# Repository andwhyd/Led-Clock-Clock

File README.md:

# LED Clock Clock
Ongoing project to create a less mechanical [Clock Clock](https://clockclock.com/collections/clockclock-24) clone.

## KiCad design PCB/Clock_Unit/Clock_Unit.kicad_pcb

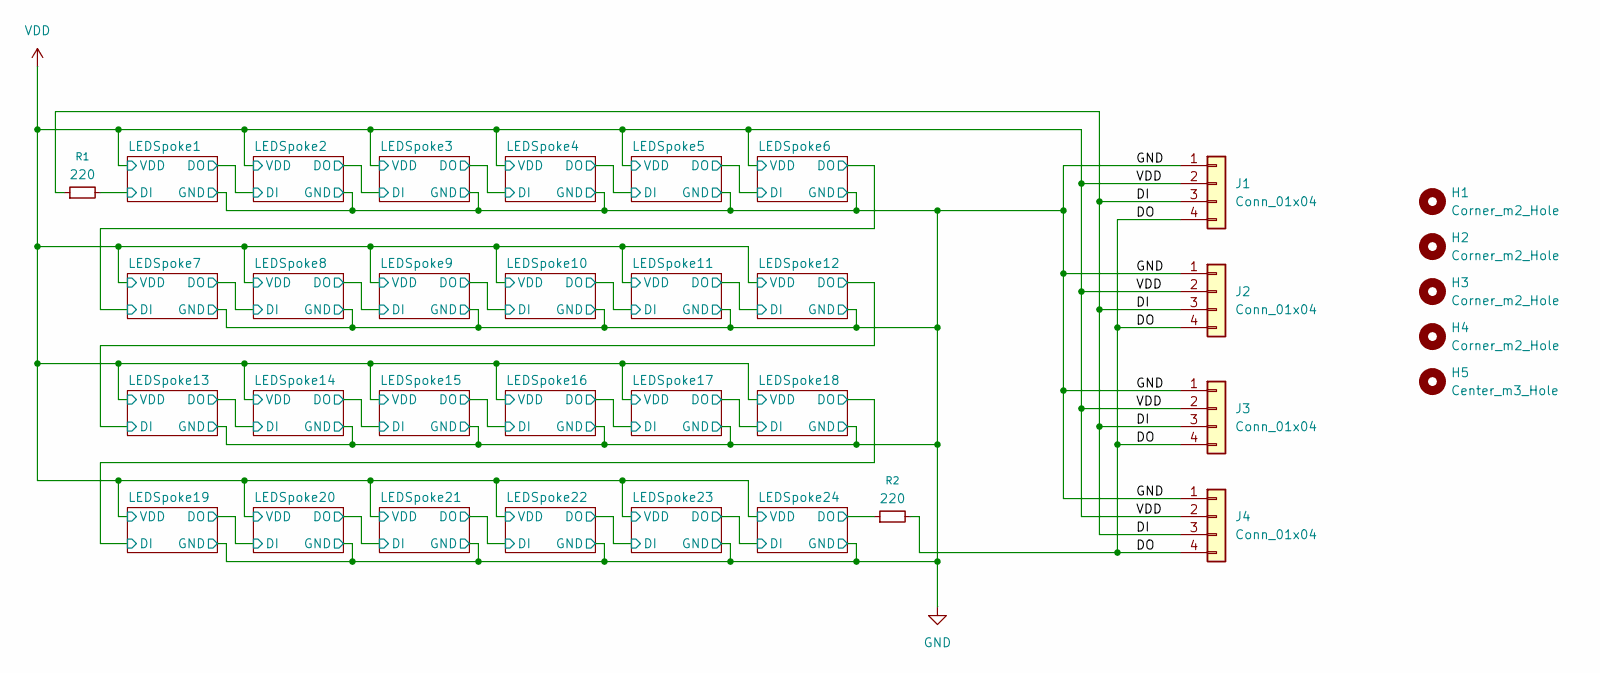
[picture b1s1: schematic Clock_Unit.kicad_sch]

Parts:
H1, H2, H3, H4: Corner_m2_Hole; MountingHole_2.2mm_M2
H5: Center_m3_Hole; MountingHole_3.2mm_M3
J1, J2, J3, J4: Conn_01x04; PinHeader_1x04_P2.54mm_Vertical
R1, R2: 220; R_0402_1005Metric_Pad0.72x0.64mm_HandSolder

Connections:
/DI: J1.3, J2.3, J3.3, J4.3, R1.1
/DO: J1.4, J2.4, J3.4, J4.4, R2.2
/LEDSpoke1/DI: R1.2; also elsewhere on the board
/LEDSpoke24/DO: R2.1; also elsewhere on the board
GND: J1.1, J2.1, J3.1, J4.1; also elsewhere on the board
VDD: J1.2, J2.2, J3.2, J4.2; also elsewhere on the board

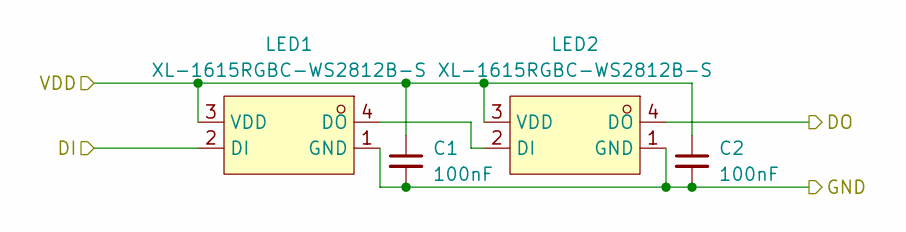
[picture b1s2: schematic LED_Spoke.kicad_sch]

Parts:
C1, C2: 100nF; C_0402_1005Metric_Pad0.74x0.62mm_HandSolder
LED1, LED2: XL-1615RGBC-WS2812B-S; LED-SMD_4P-L1.6-W1.5_XL-1615RGBC-WS2812B-S; LCSC Part C41413180

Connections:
/LEDSpoke1/DI: LED1.2 (DI); also elsewhere on the board
/LEDSpoke1/DO: LED2.4 (DO); also elsewhere on the board
GND: C1.2, C2.2, LED1.1 (GND), LED2.1 (GND); also elsewhere on the board
unnamed: LED1.4 (DO), LED2.2 (DI)
VDD: C1.1, C2.1, LED1.3 (VDD), LED2.3 (VDD); also elsewhere on the board

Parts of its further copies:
C3, C4, C5, C6, C7, C8, C9, C10, C11, C12, C13, C14, C15, C16, C17, C18, C19, C20, C21, C22, C23, C24, C25, C26, C27, C28, C29, C30, C31, C32, C33, C34, C35, C36, C37, C38, C39, C40, C41, C42, C43, C44, C45, C46, C47, C48: 100nF; C_0402_1005Metric_Pad0.74x0.62mm_HandSolder
LED3, LED4, LED5, LED6, LED7, LED8, LED9, LED10, LED11, LED12, LED13, LED14, LED15, LED16, LED17, LED18, LED19, LED20, LED21, LED22, LED23, LED24, LED25, LED26, LED27, LED28, LED29, LED30, LED31, LED32, LED33, LED34, LED35, LED36, LED37, LED38, LED39, LED40, LED41, LED42, LED43, LED44, LED45, LED46, LED47, LED48: XL-1615RGBC-WS2812B-S; LED-SMD_4P-L1.6-W1.5_XL-1615RGBC-WS2812B-S; LCSC Part C41413180

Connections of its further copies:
/LEDSpoke1/DO: LED3.2 (DI); also elsewhere on the board
/LEDSpoke2/DO: LED4.4 (DO), LED5.2 (DI)
/LEDSpoke3/DO: LED6.4 (DO), LED7.2 (DI)
/LEDSpoke4/DO: LED8.4 (DO), LED9.2 (DI)
/LEDSpoke5/DO: LED10.4 (DO), LED11.2 (DI)
/LEDSpoke6/DO: LED12.4 (DO), LED13.2 (DI)
/LEDSpoke7/DO: LED14.4 (DO), LED15.2 (DI)
/LEDSpoke8/DO: LED16.4 (DO), LED17.2 (DI)
/LEDSpoke10/DI: LED18.4 (DO), LED19.2 (DI)
/LEDSpoke10/DO: LED20.4 (DO), LED21.2 (DI)
/LEDSpoke11/DO: LED22.4 (DO), LED23.2 (DI)
/LEDSpoke12/DO: LED24.4 (DO), LED25.2 (DI)
/LEDSpoke13/DO: LED26.4 (DO), LED27.2 (DI)
/LEDSpoke14/DO: LED28.4 (DO), LED29.2 (DI)
/LEDSpoke15/DO: LED30.4 (DO), LED31.2 (DI)
/LEDSpoke16/DO: LED32.4 (DO), LED33.2 (DI)
/LEDSpoke17/DO: LED34.4 (DO), LED35.2 (DI)
/LEDSpoke18/DO: LED36.4 (DO), LED37.2 (DI)
/LEDSpoke19/DO: LED38.4 (DO), LED39.2 (DI)
/LEDSpoke20/DO: LED40.4 (DO), LED41.2 (DI)
/LEDSpoke21/DO: LED42.4 (DO), LED43.2 (DI)
/LEDSpoke22/DO: LED44.4 (DO), LED45.2 (DI)
/LEDSpoke23/DO: LED46.4 (DO), LED47.2 (DI)
/LEDSpoke24/DO: LED48.4 (DO); also elsewhere on the board
GND: C3.2, C4.2, C5.2, C6.2, C7.2, C8.2, C9.2, C10.2, C11.2, C12.2, C13.2, C14.2, C15.2, C16.2, C17.2, C18.2, C19.2, C20.2, C21.2, C22.2, C23.2, C24.2, C25.2, C26.2, C27.2, C28.2, C29.2, C30.2, C31.2, C32.2, C33.2, C34.2, C35.2, C36.2, C37.2, C38.2, C39.2, C40.2, C41.2, C42.2, C43.2, C44.2, C45.2, C46.2, C47.2, C48.2, LED3.1 (GND), LED4.1 (GND), LED5.1 (GND), LED6.1 (GND), LED7.1 (GND), LED8.1 (GND), LED9.1 (GND), LED10.1 (GND), LED11.1 (GND), LED12.1 (GND), LED13.1 (GND), LED14.1 (GND), LED15.1 (GND), LED16.1 (GND), LED17.1 (GND), LED18.1 (GND), LED19.1 (GND), LED20.1 (GND), LED21.1 (GND), LED22.1 (GND), LED23.1 (GND), LED24.1 (GND), LED25.1 (GND), LED26.1 (GND), LED27.1 (GND), LED28.1 (GND), LED29.1 (GND), LED30.1 (GND), LED31.1 (GND), LED32.1 (GND), LED33.1 (GND), LED34.1 (GND), LED35.1 (GND), LED36.1 (GND), LED37.1 (GND), LED38.1 (GND), LED39.1 (GND), LED40.1 (GND), LED41.1 (GND), LED42.1 (GND), LED43.1 (GND), LED44.1 (GND), LED45.1 (GND), LED46.1 (GND), LED47.1 (GND), LED48.1 (GND); also elsewhere on the board
unnamed: LED3.4 (DO), LED4.2 (DI)
unnamed: LED5.4 (DO), LED6.2 (DI)
unnamed: LED7.4 (DO), LED8.2 (DI)
unnamed: LED9.4 (DO), LED10.2 (DI)
unnamed: LED11.4 (DO), LED12.2 (DI)
unnamed: LED13.4 (DO), LED14.2 (DI)
unnamed: LED15.4 (DO), LED16.2 (DI)
unnamed: LED17.4 (DO), LED18.2 (DI)
unnamed: LED19.4 (DO), LED20.2 (DI)
unnamed: LED21.4 (DO), LED22.2 (DI)
unnamed: LED23.4 (DO), LED24.2 (DI)
unnamed: LED25.4 (DO), LED26.2 (DI)
unnamed: LED27.4 (DO), LED28.2 (DI)
unnamed: LED29.4 (DO), LED30.2 (DI)
unnamed: LED31.4 (DO), LED32.2 (DI)
unnamed: LED33.4 (DO), LED34.2 (DI)
unnamed: LED35.4 (DO), LED36.2 (DI)
unnamed: LED37.4 (DO), LED38.2 (DI)
unnamed: LED39.4 (DO), LED40.2 (DI)
unnamed: LED41.4 (DO), LED42.2 (DI)
unnamed: LED43.4 (DO), LED44.2 (DI)
unnamed: LED45.4 (DO), LED46.2 (DI)
unnamed: LED47.4 (DO), LED48.2 (DI)
VDD: C3.1, C4.1, C5.1, C6.1, C7.1, C8.1, C9.1, C10.1, C11.1, C12.1, C13.1, C14.1, C15.1, C16.1, C17.1, C18.1, C19.1, C20.1, C21.1, C22.1, C23.1, C24.1, C25.1, C26.1, C27.1, C28.1, C29.1, C30.1, C31.1, C32.1, C33.1, C34.1, C35.1, C36.1, C37.1, C38.1, C39.1, C40.1, C41.1, C42.1, C43.1, C44.1, C45.1, C46.1, C47.1, C48.1, LED3.3 (VDD), LED4.3 (VDD), LED5.3 (VDD), LED6.3 (VDD), LED7.3 (VDD), LED8.3 (VDD), LED9.3 (VDD), LED10.3 (VDD), LED11.3 (VDD), LED12.3 (VDD), LED13.3 (VDD), LED14.3 (VDD), LED15.3 (VDD), LED16.3 (VDD), LED17.3 (VDD), LED18.3 (VDD), LED19.3 (VDD), LED20.3 (VDD), LED21.3 (VDD), LED22.3 (VDD), LED23.3 (VDD), LED24.3 (VDD), LED25.3 (VDD), LED26.3 (VDD), LED27.3 (VDD), LED28.3 (VDD), LED29.3 (VDD), LED30.3 (VDD), LED31.3 (VDD), LED32.3 (VDD), LED33.3 (VDD), LED34.3 (VDD), LED35.3 (VDD), LED36.3 (VDD), LED37.3 (VDD), LED38.3 (VDD), LED39.3 (VDD), LED40.3 (VDD), LED41.3 (VDD), LED42.3 (VDD), LED43.3 (VDD), LED44.3 (VDD), LED45.3 (VDD), LED46.3 (VDD), LED47.3 (VDD), LED48.3 (VDD); also elsewhere on the board

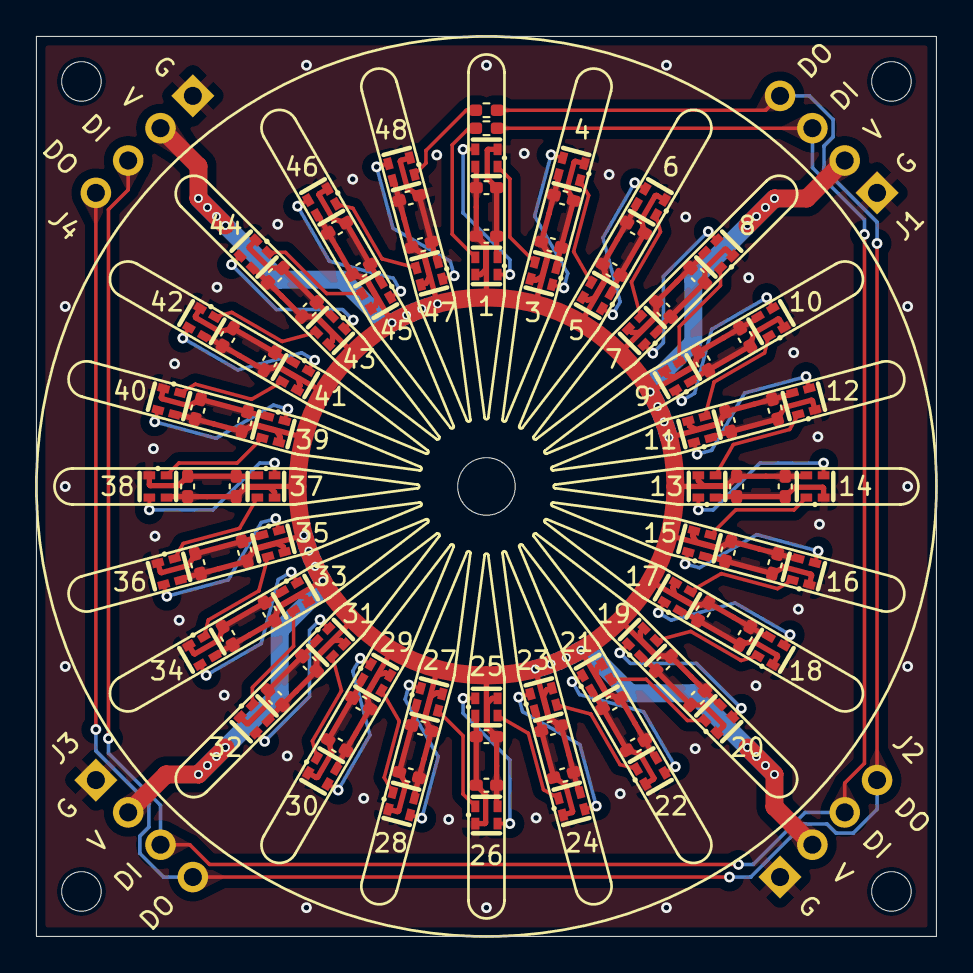
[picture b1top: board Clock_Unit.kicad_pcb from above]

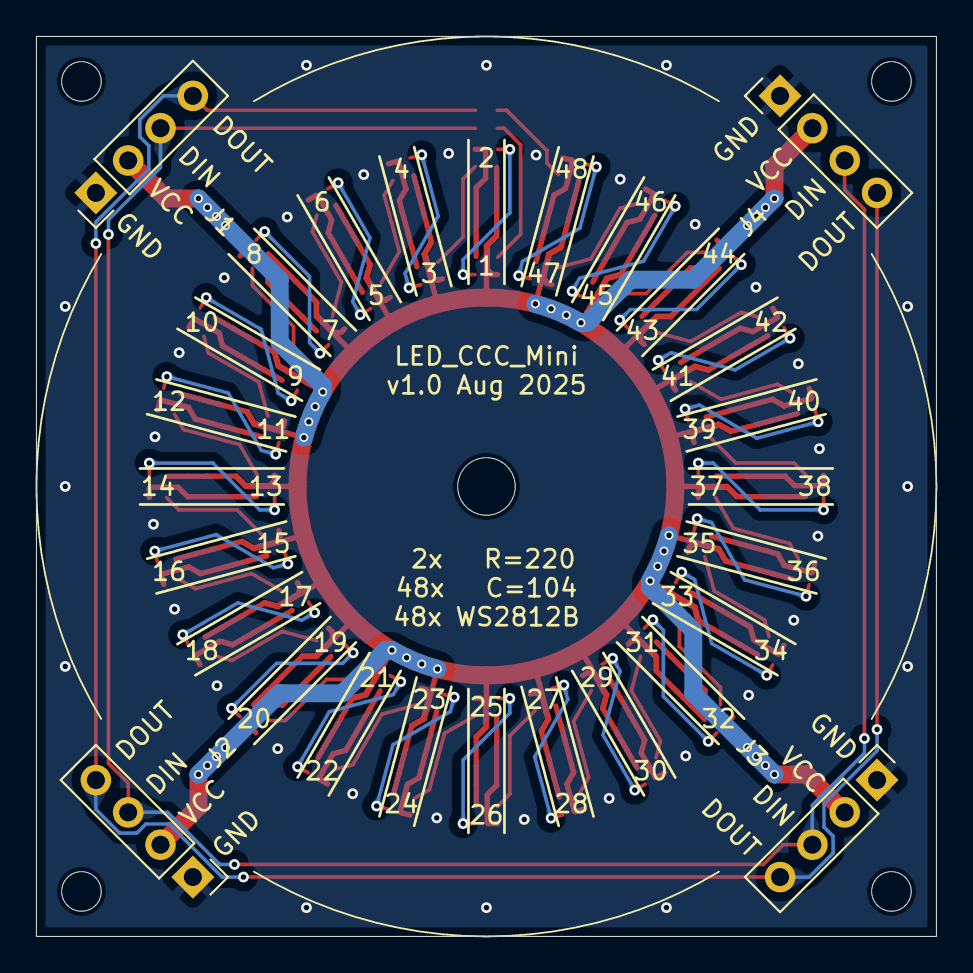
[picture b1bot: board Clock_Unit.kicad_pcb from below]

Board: 2 copper layers, 50.0 x 50.0 mm, 107 parts (4 on the bottom side), 53 nets.

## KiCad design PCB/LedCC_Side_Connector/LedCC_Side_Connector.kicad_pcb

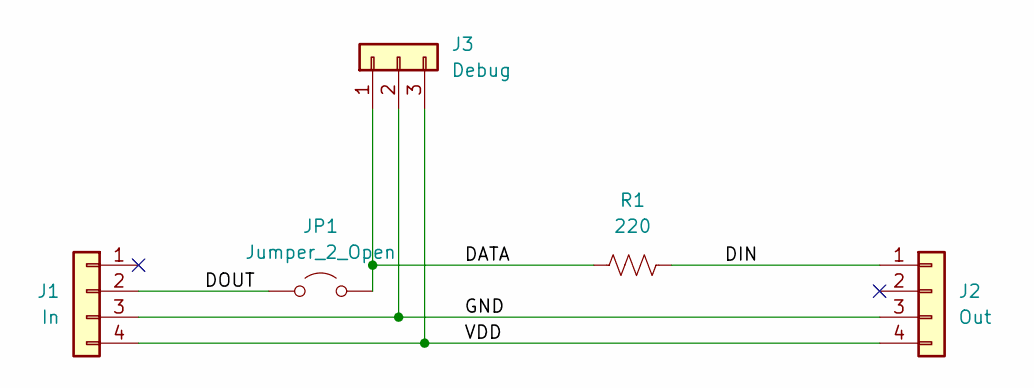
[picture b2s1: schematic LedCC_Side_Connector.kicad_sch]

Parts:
J1: In; HDR-TH_4P-P1.27-V-F-R2-C2-S1.27
J2: Out; HDR-TH_4P-P1.27-V-F-R2-C2-S1.27
J3: Debug; PinSocket_1x03_P2.54mm_Vertical
JP1: Jumper_2_Open; SolderJumper-2_P1.3mm_Open_RoundedPad1.0x1.5mm
R1: 220; R_0603_1608Metric

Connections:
/DATA: J3.1, JP1.2 (B), R1.1
/DIN: J2.1, R1.2
/DOUT: J1.2, JP1.1 (A)
/GND: J1.3, J2.3, J3.2
/VDD: J1.4, J2.4, J3.3

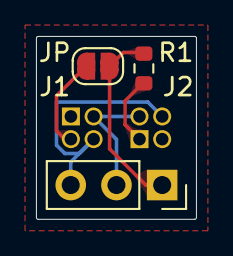
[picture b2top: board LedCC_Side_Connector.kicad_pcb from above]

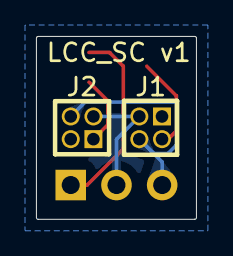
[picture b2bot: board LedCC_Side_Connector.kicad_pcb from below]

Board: 2 copper layers, 8.9 x 10.2 mm, 5 parts (2 on the bottom side), 5 nets.

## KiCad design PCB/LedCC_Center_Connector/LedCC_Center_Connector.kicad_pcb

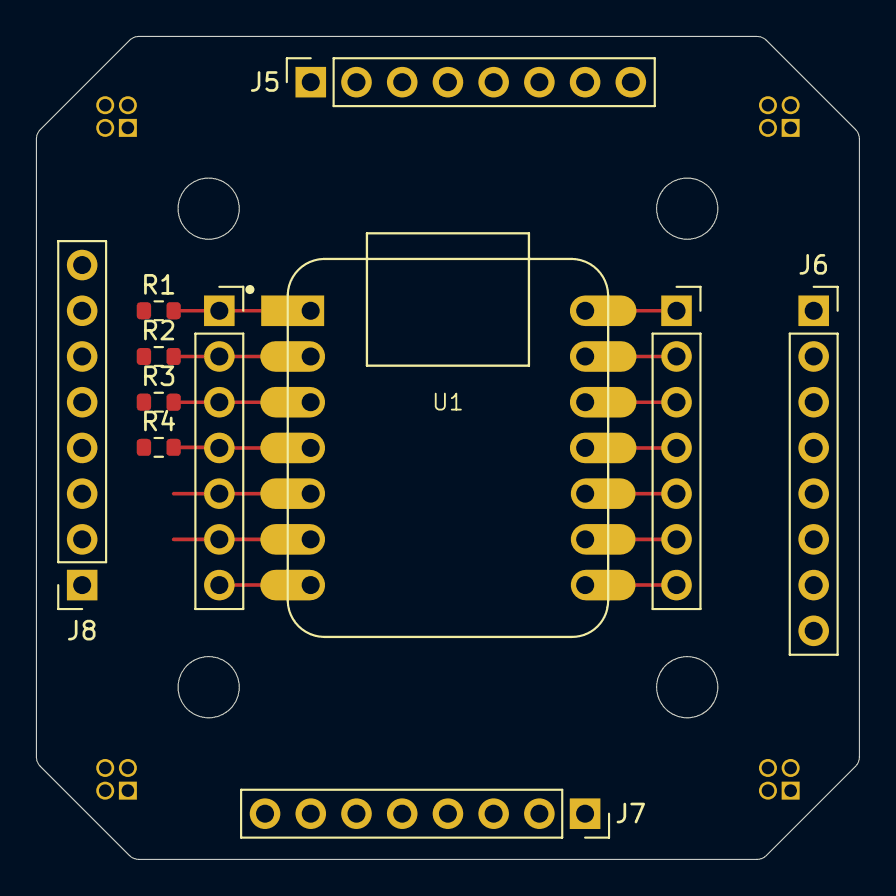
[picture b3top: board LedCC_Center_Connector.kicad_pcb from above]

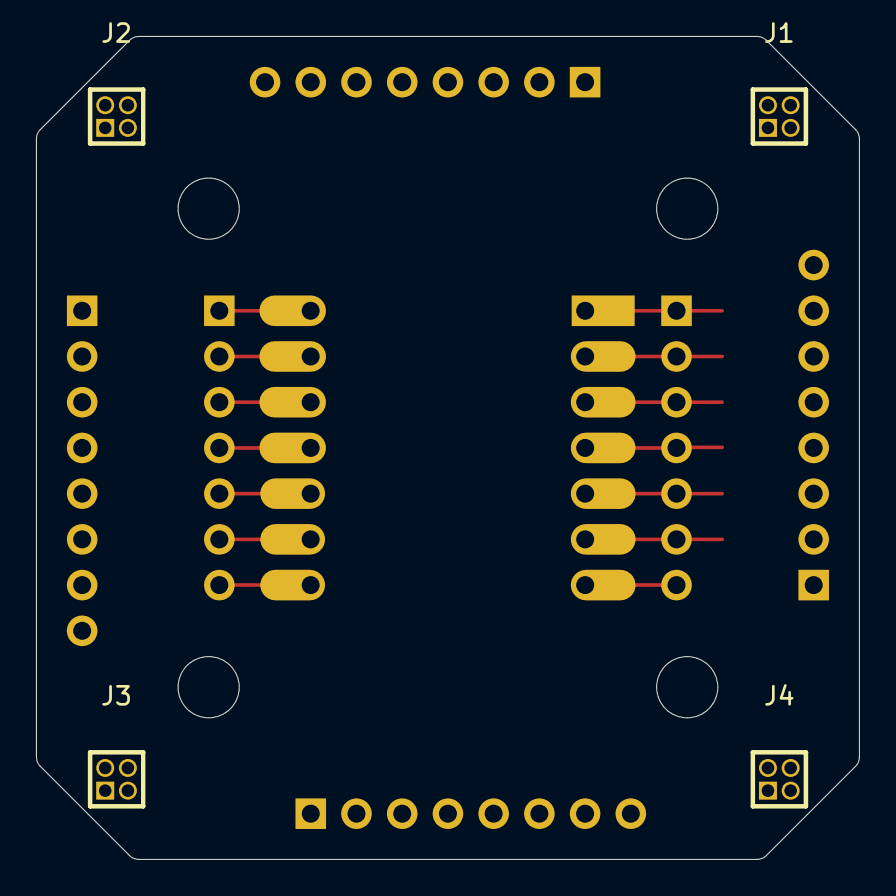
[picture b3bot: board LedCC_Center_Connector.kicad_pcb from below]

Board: 2 copper layers, 45.7 x 45.7 mm, 15 parts (4 on the bottom side), 18 nets.

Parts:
J1: LED1; HDR-TH_4P-P1.27-V-F-R2-C2-S1.27
J2: LED2; HDR-TH_4P-P1.27-V-F-R2-C2-S1.27
J3: LED3; HDR-TH_4P-P1.27-V-F-R2-C2-S1.27
J4: LED4; HDR-TH_4P-P1.27-V-F-R2-C2-S1.27
J5, J6, J7, J8: Conn_01x06; PinSocket_1x08_P2.54mm_Vertical
J9, J10: Conn_01x07; PinSocket_1x07_P2.54mm_Vertical
R1, R2, R3, R4: 220; R_0603_1608Metric
U1: Seeed Studio XIAO SAMD21; XIAO-Generic-Hybrid-14P-2.54-21X17.8MM

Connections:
/DIN1: J1.1, R1.1
/DIN2: J2.1, R2.1
/DIN3: J3.1, R3.1
/DIN4: J4.1, R4.1
/GND: J1.4, J2.4, J3.4, J4.4, J5.2, J6.2, J7.2, J8.2, J10.1, U1.14 (5V)
/VDD: J1.3, J2.3, J3.3, J4.3, J5.1, J6.1, J7.1, J8.1, J10.2, U1.13 (GND)
unnamed: J5.3, J6.3, J7.3, J8.3, J9.1, U1.1 (PA02_A0_D0)
unnamed: J5.4, J6.4, J7.4, J8.4, J9.2, U1.2 (PA4_A1_D1)
unnamed: J5.5, J6.5, J7.5, J8.5, J9.3, U1.3 (PA10_A2_D2)
unnamed: J5.6, J6.6, J7.6, J8.6, J9.4, U1.4 (PA11_A3_D3)
unnamed: J5.7, J6.7, J7.7, J8.7, J9.5, U1.5 (PA8_A4_D4_SDA)
unnamed: J5.8, J6.8, J7.8, J8.8, J9.6, U1.6 (PA9_A5_D5_SCL)
unnamed: J9.7, U1.7 (PB08_A6_D6_TX)
unnamed: J10.3, U1.12 (3V3)
unnamed: J10.4, U1.11 (PA6_A10_D10_MOSI)
unnamed: J10.5, U1.10 (PA5_A9_D9_MISO)
unnamed: J10.6, U1.9 (PA7_A8_D8_SCK)
unnamed: J10.7, U1.8 (PB09_A7_D7_RX)

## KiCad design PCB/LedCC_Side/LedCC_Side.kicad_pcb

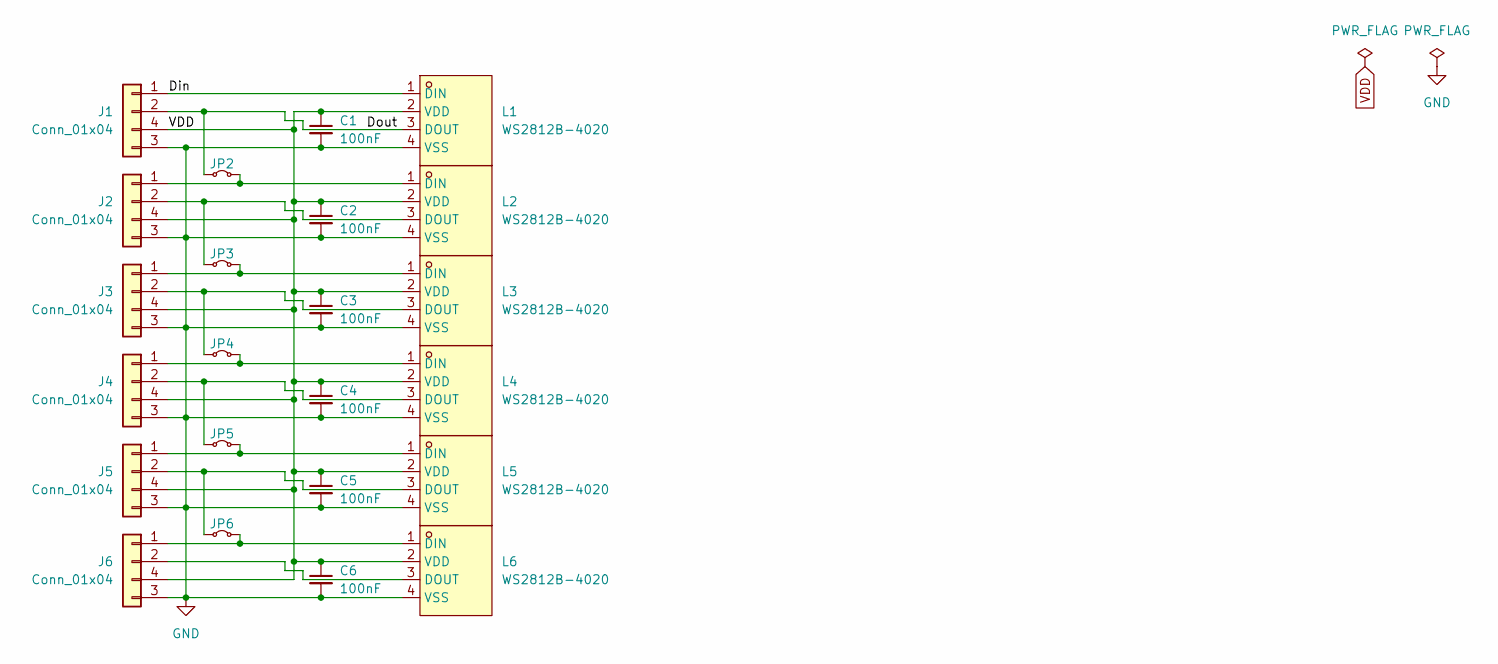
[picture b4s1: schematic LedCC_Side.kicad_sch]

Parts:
C1, C2, C3, C4, C5, C6: 100nF; C_0603_1608Metric
J1, J2, J3, J4, J5, J6: Conn_01x04; HDR-SMD_4P-P1.27-V-M-R2-C2-S1.27-LS5.5
JP2, JP3, JP4, JP5, JP6: Jumper_2_Small_Bridged; SolderJumper-2_P1.3mm_Bridged_RoundedPad1.0x1.5mm
L1, L2, L3, L4, L5, L6: WS2812B-4020; LED-SMD_WS2812B-4020; LCSC Part C965557

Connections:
/Din: J1.1, L1.1 (DIN)
/Dout: J1.2, JP2.1 (A), L1.3 (DOUT)
GND: C1.2, C2.2, C3.2, C4.2, C5.2, C6.2, J1.3, J2.3, J3.3, J4.3, J5.3, J6.3, L1.4 (VSS), L2.4 (VSS), L3.4 (VSS), L4.4 (VSS), L5.4 (VSS), L6.4 (VSS)
unnamed: J2.1, JP2.2 (B), L2.1 (DIN)
unnamed: J2.2, JP3.1 (A), L2.3 (DOUT)
unnamed: J3.1, JP3.2 (B), L3.1 (DIN)
unnamed: J3.2, JP4.1 (A), L3.3 (DOUT)
unnamed: J4.1, JP4.2 (B), L4.1 (DIN)
unnamed: J4.2, JP5.1 (A), L4.3 (DOUT)
unnamed: J5.1, JP5.2 (B), L5.1 (DIN)
unnamed: J5.2, JP6.1 (A), L5.3 (DOUT)
unnamed: J6.1, JP6.2 (B), L6.1 (DIN)
unnamed: J6.2, L6.3 (DOUT)
VDD: C1.1, C2.1, C3.1, C4.1, C5.1, C6.1, J1.4, J2.4, J3.4, J4.4, J5.4, J6.4, L1.2 (VDD), L2.2 (VDD), L3.2 (VDD), L4.2 (VDD), L5.2 (VDD), L6.2 (VDD)

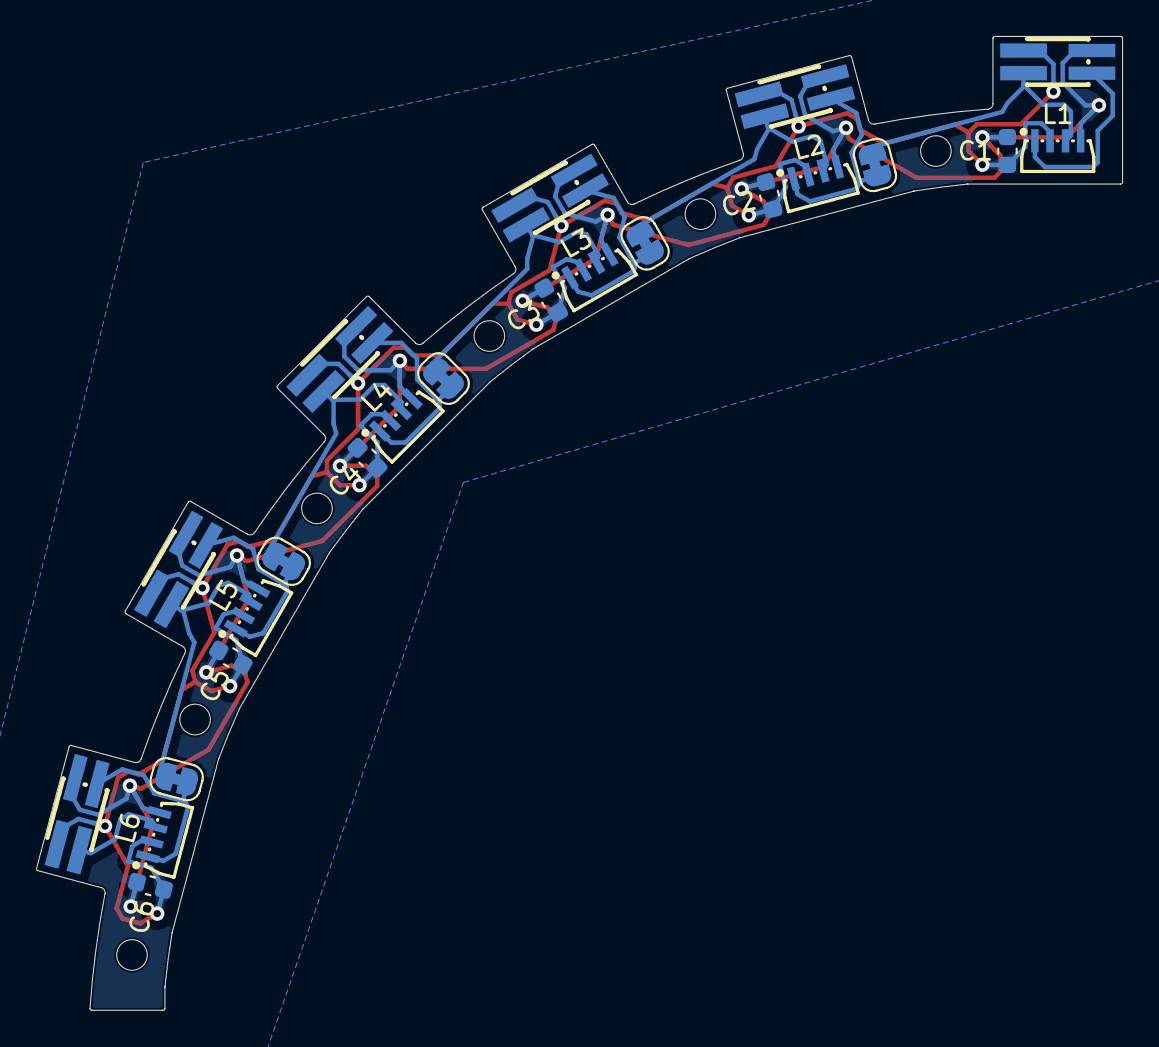
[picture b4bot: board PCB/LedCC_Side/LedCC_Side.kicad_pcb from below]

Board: 2 copper layers, 60.3 x 54.1 mm, 23 parts (23 on the bottom side), 14 nets.

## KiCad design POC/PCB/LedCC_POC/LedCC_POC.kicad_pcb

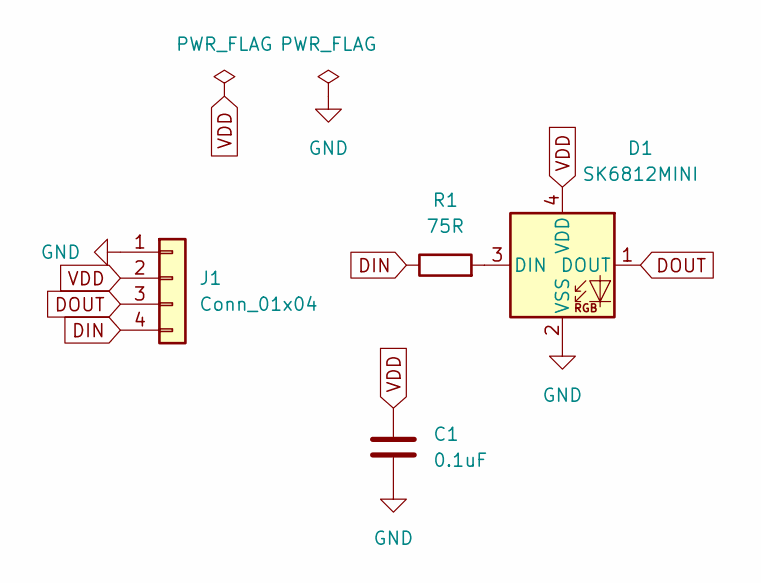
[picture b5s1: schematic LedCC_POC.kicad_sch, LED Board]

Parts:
C1: 0.1uF; C_0805_2012Metric_Pad1.18x1.45mm_HandSolder
D1: SK6812MINI; SK6812-MINI-E
J1: Conn_01x04; SolderWirePad_1x04_SMD_1x2mm
R1: 75R; R_0805_2012Metric_Pad1.20x1.40mm_HandSolder

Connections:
DIN: J1.4, R1.1
DOUT: D1.1 (DOUT), J1.3
GND: C1.1, D1.2 (VSS), J1.1
unnamed: D1.3 (DIN), R1.2
VDD: C1.2, D1.4 (VDD), J1.2

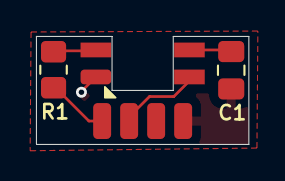
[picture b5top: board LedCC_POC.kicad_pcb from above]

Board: 2 copper layers, 11.8 x 6.0 mm, 4 parts (0 on the bottom side), 5 nets.

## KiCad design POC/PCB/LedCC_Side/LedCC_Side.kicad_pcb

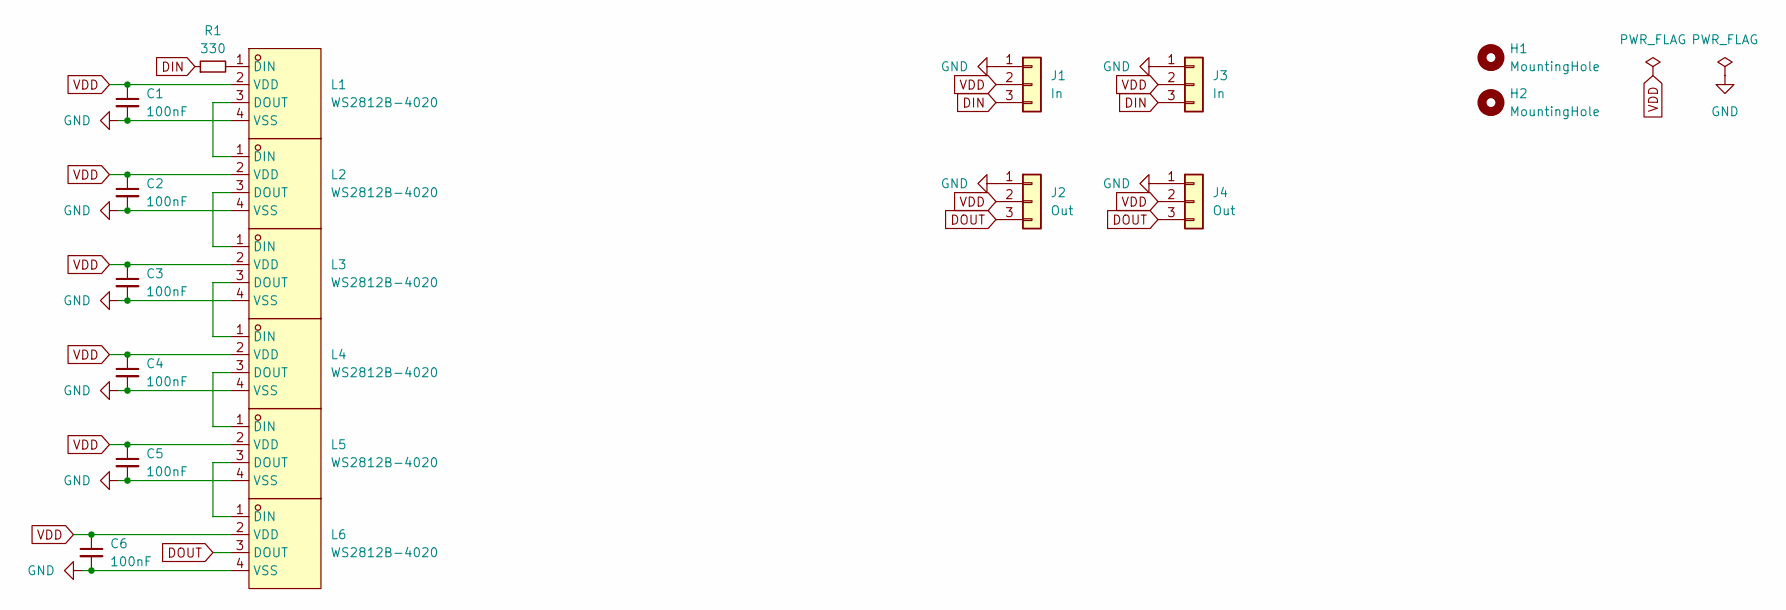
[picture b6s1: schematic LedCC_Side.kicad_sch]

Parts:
C1, C2, C3, C4, C5, C6: 100nF; C_0603_1608Metric
H1, H2: MountingHole; MountingHole_2.2mm_M2
J1, J3: In; Led-Jumper
J2, J4: Out; Led-Jumper
L1, L2, L3, L4, L5, L6: WS2812B-4020; LED-SMD_WS2812B-4020; LCSC Part C965557
R1: 330; R_0603_1608Metric

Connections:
DIN: J1.3, J3.3, R1.1
DOUT: J2.3, J4.3, L6.3 (DOUT)
GND: C1.2, C2.2, C3.2, C4.2, C5.2, C6.2, J1.1, J2.1, J3.1, J4.1, L1.4 (VSS), L2.4 (VSS), L3.4 (VSS), L4.4 (VSS), L5.4 (VSS), L6.4 (VSS)
unnamed: L1.1 (DIN), R1.2
unnamed: L1.3 (DOUT), L2.1 (DIN)
unnamed: L2.3 (DOUT), L3.1 (DIN)
unnamed: L3.3 (DOUT), L4.1 (DIN)
unnamed: L4.3 (DOUT), L5.1 (DIN)
unnamed: L5.3 (DOUT), L6.1 (DIN)
VDD: C1.1, C2.1, C3.1, C4.1, C5.1, C6.1, J1.2, J2.2, J3.2, J4.2, L1.2 (VDD), L2.2 (VDD), L3.2 (VDD), L4.2 (VDD), L5.2 (VDD), L6.2 (VDD)

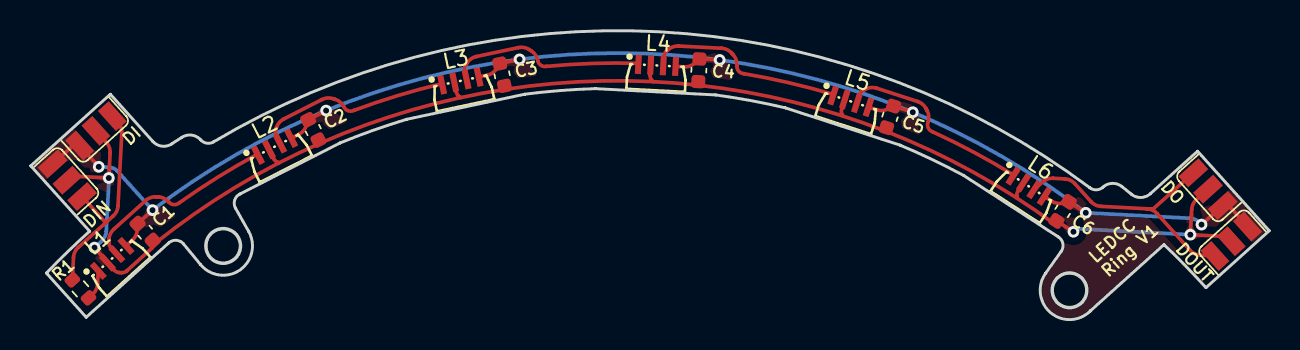
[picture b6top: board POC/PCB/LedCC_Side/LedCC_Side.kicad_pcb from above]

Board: 2 copper layers, 84.5 x 19.7 mm, 19 parts (0 on the bottom side), 10 nets.

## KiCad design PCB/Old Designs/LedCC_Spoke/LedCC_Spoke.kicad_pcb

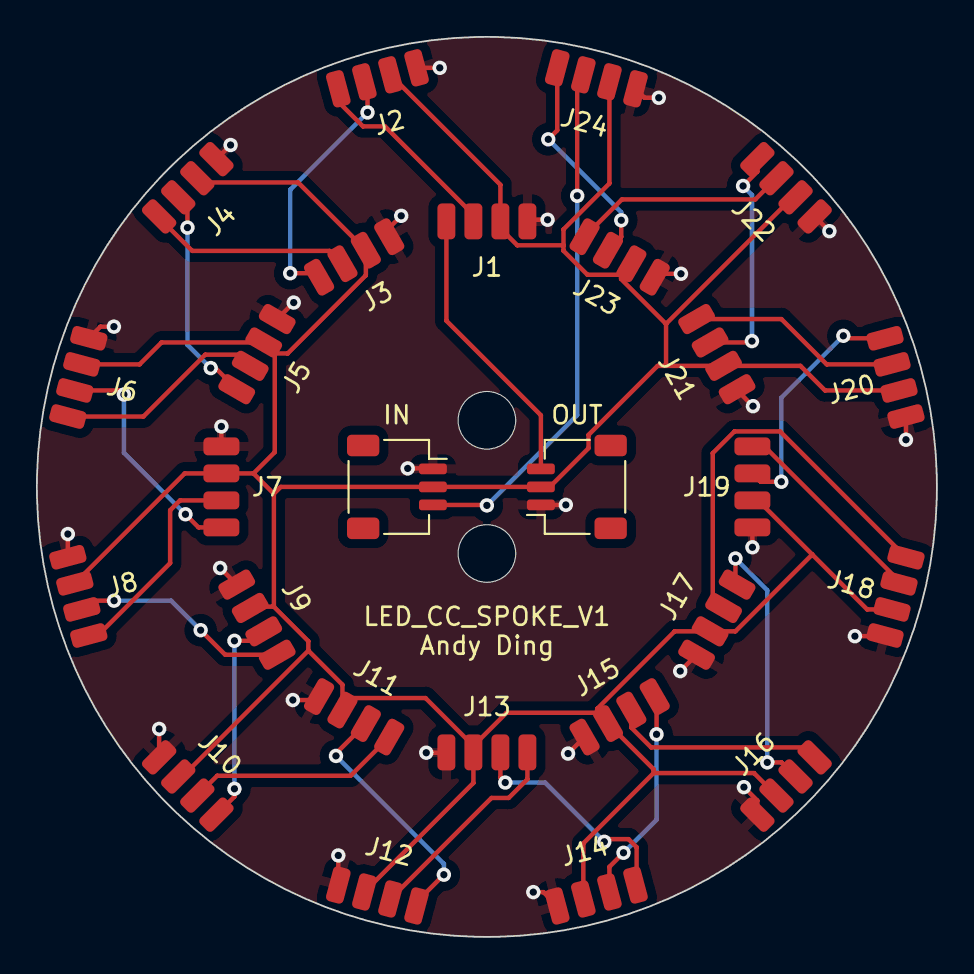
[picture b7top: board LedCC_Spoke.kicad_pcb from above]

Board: 2 copper layers, 50.0 x 50.0 mm, 26 parts (0 on the bottom side), 27 nets.

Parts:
IN: In; JST_SH_SM03B-SRSS-TB_1x03-1MP_P1.00mm_Horizontal
J1, J2, J3, J4, J5, J6, J7, J8, J9, J10, J11, J12, J13, J14, J15, J16, J17, J18, J19, J20, J21, J22, J23, J24: Conn_01x04; SolderWirePad_1x04_SMD_1x2mm
OUT: Out; JST_SH_SM03B-SRSS-TB_1x03-1MP_P1.00mm_Horizontal

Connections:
DIN: IN.3, J24.3
DOUT: J1.4, OUT.3
GND: IN.1, J1.1, J2.1, J3.1, J4.1, J5.1, J6.1, J7.1, J8.1, J9.1, J10.1, J11.1, J12.1, J13.1, J14.1, J15.1, J16.1, J17.1, J18.1, J19.1, J20.1, J21.1, J22.1, J23.1, J24.1, OUT.1
unnamed: J1.3, J2.4
unnamed: J2.3, J3.4
unnamed: J3.3, J4.4
unnamed: J4.3, J5.4
unnamed: J5.3, J6.4
unnamed: J6.3, J7.4
unnamed: J7.3, J8.4
unnamed: J8.3, J9.4
unnamed: J10.3, J11.4
unnamed: J9.3, J10.4
unnamed: J11.3, J12.4
unnamed: J12.3, J13.4
unnamed: J13.3, J14.4
unnamed: J14.3, J15.4
unnamed: J15.3, J16.4
unnamed: J16.3, J17.4
unnamed: J17.3, J18.4
unnamed: J18.3, J19.4
unnamed: J19.3, J20.4
unnamed: J20.3, J21.4
unnamed: J21.3, J22.4
unnamed: J22.3, J23.4
unnamed: J23.3, J24.4
VDD: IN.2, J1.2, J2.2, J3.2, J4.2, J5.2, J6.2, J7.2, J8.2, J9.2, J10.2, J11.2, J12.2, J13.2, J14.2, J15.2, J16.2, J17.2, J18.2, J19.2, J20.2, J21.2, J22.2, J23.2, J24.2, OUT.2

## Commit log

2024-01-01 Update '5' digit
2024-05-20 Add PCB
2024-06-10 Testing code updates
2024-06-10 Reorganize files
2024-06-21 Reorganize
2024-06-21 Prototype digit testing
2024-07-14 PCB Updates
2025-08-18 Pivot to smaller design with simpler PCB
    Change from side lit LEDs and 4 piece circles to 50mm smaller flat PCBs and diffused 1.5mm LEDs
2025-08-18 Increase VDD trace width
    Chanced from 0.3mm to 1mm to support max power draw of all LEDs
2025-08-18 Add center hole
    m3 opening added
2025-08-19 Schematic + PCB Updates
    Corrected LED symbol and improved silkscreen
2025-08-19 Presentation Update
    Make barely presentable
2025-08-19 Clean up repo
2025-08-19 Add Plots
2025-08-20 Plots added
